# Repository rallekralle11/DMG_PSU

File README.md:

Now tested and confirmed functional.

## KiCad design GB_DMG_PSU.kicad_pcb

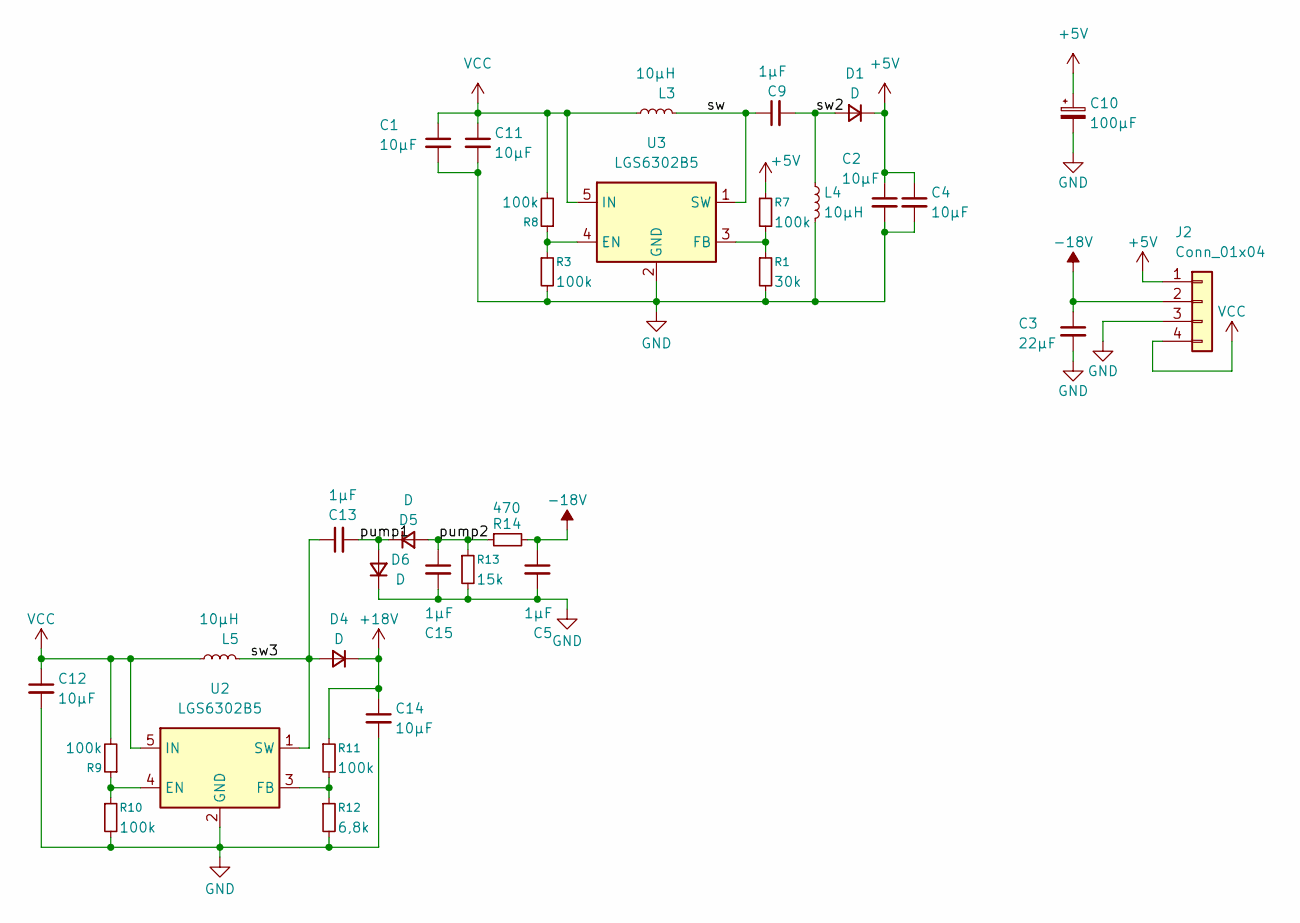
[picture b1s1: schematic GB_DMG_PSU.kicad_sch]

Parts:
C1, C2, C4, C11, C12, C14: 10µF; C_0805_2012Metric
C3: 22µF; C_1206_3216Metric
C5, C9, C13, C15: 1µF; C_0603_1608Metric
C10: 100µF; C_1206_3216Metric
D1, D4, D5, D6: D; D_SOD-323
J2: Conn_01x04; PinHeader_1x04_P2.54mm_Vertical
L3, L4, L5: 10µH; L_APV_ANR5040
R1: 30k; R_0603_1608Metric
R3, R7, R8, R9, R10, R11: 100k; R_0603_1608Metric
R12: 6,8k; R_0603_1608Metric
R13: 15k; R_0603_1608Metric
R14: 470; R_0603_1608Metric
U2, U3: LGS6302B5; SOT-23-5

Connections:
+5V: C2.1, C4.1, C10.1, D1.1 (K), J2.1, R7.1
+18V: C14.1, D4.1 (K), R11.1
-18V: C3.1, C5.1, J2.2, R14.2
/pump1: C13.2, D5.1 (K), D6.2 (A)
/pump2: C15.1, D5.2 (A), R13.1, R14.1
/sw: C9.1, L3.2, U3.1 (SW)
/sw2: C9.2, D1.2 (A), L4.1
/sw3: C13.1, D4.2 (A), L5.2, U2.1 (SW)
GND: C1.2, C2.2, C3.2, C4.2, C5.2, C10.2, C11.2, C12.2, C14.2, C15.2, D6.1 (K), J2.3, L4.2, R1.2, R3.2, R10.2, R12.2, R13.2, U2.2 (GND), U3.2 (GND)
unnamed: R9.1, R10.1, U2.4 (EN)
unnamed: R11.2, R12.1, U2.3 (FB)
unnamed: R3.1, R8.1, U3.4 (EN)
unnamed: R1.1, R7.2, U3.3 (FB)
VCC: C1.1, C11.1, C12.1, J2.4, L3.1, L5.1, R8.2, R9.2, U2.5 (IN), U3.5 (IN)

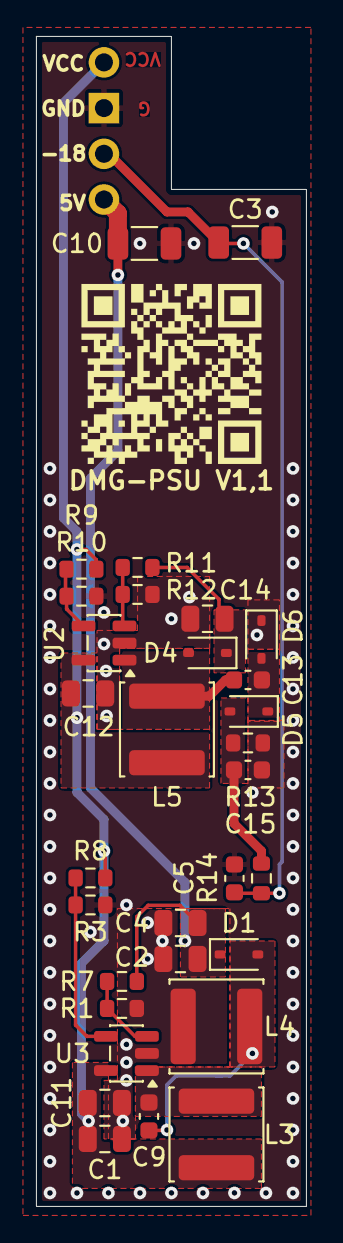
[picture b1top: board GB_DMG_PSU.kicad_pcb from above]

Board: 2 copper layers, 15.0 x 65.0 mm, 32 parts (0 on the bottom side), 14 nets.

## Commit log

2025-10-09 init
2025-10-09 final touches
2025-10-09 pictures
2025-10-09 manufacturing files
2025-10-09 don't need backups online
2025-10-24 more changes
2025-10-29 some things i missed
2025-10-29 final tweaks before manufacture
2025-11-26 bit of a redo
2025-11-26 clearing some backups
2025-11-26 moved some vias
2025-11-27 BOM/gerbers

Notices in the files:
GB_DMG_PSU.kicad_pcb:
CERN-OHL-P
